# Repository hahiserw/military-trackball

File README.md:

# Military trackball

## Main document - main.pdf

## Youtube demo

## Gallery

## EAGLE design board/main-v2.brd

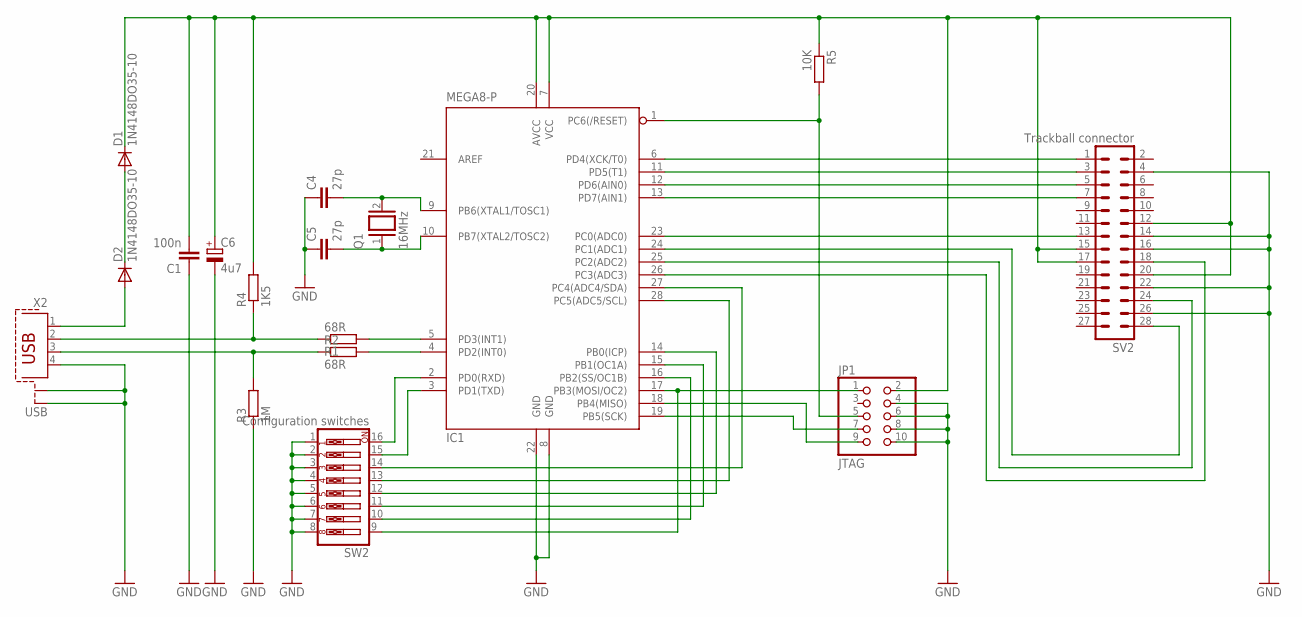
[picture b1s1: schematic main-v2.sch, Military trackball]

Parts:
C1: 100n; C025-025X050
C4, C5: 27p; C025-025X050
C6: 4u7; E2,5-5
D1, D2: 1N4148DO35-10; DO35-10
IC1: MEGA8-P; DIL28-3
JP1: JTAG; 2X05
Q1: 16MHz; QS
R1, R2: 68R; 0207/10
R3: 1M; 0207/10
R4: 1K5; 0207/10
R5: 10K; 0207/10
SV2: Trackball connector; MA14-2
SW2: Configuration switches; EDG-08
X2: USB; PN61729-S

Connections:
GND: C1.1, C4.1, C5.1, C6.-, IC1.8 (GND), IC1.22 (GND), JP1.4, JP1.6, JP1.8, JP1.10, R3.1, SV2.4, SV2.14, SV2.16, SV2.22, SV2.26, SW2.1, SW2.2, SW2.3, SW2.4, SW2.5, SW2.6, SW2.7, SW2.8, X2.4, X2.S1, X2.S2
unnamed: D1.A, D2.C
unnamed: IC1.5 (PD3(INT1)), R1.2
unnamed: IC1.4 (PD2(INT0)), R2.2
unnamed: R1.1, R4.1, X2.2
unnamed: R2.1, R3.2, X2.3
unnamed: IC1.12 (PD6(AIN0)), SV2.5
unnamed: C5.2, IC1.10 (PB7(XTAL2/TOSC2)), Q1.1
unnamed: C4.2, IC1.9 (PB6(XTAL1/TOSC1)), Q1.2
unnamed: IC1.11 (PD5(T1)), SV2.3
unnamed: IC1.6 (PD4(XCK/T0)), SV2.1
unnamed: IC1.23 (PC0(ADC0)), SV2.13
unnamed: IC1.13 (PD7(AIN1)), SV2.7
unnamed: IC1.25 (PC2(ADC2)), SV2.24
unnamed: IC1.26 (PC3(ADC3)), SV2.18
unnamed: IC1.1 (PC6(/RESET)), JP1.5, R5.2
unnamed: IC1.18 (PB4(MISO)), JP1.9
unnamed: IC1.19 (PB5(SCK)), JP1.7
unnamed: IC1.17 (PB3(MOSI/OC2)), JP1.1, SW2.9
unnamed: IC1.24 (PC1(ADC1)), SV2.28
unnamed: D2.A, X2.1
unnamed: IC1.16 (PB2(SS/OC1B)), SW2.10
unnamed: IC1.15 (PB1(OC1A)), SW2.11
unnamed: IC1.14 (PB0(ICP)), SW2.12
unnamed: IC1.2 (PD0(RXD)), SW2.16
unnamed: IC1.3 (PD1(TXD)), SW2.15
unnamed: IC1.27 (PC4(ADC4/SDA)), SW2.14
unnamed: IC1.28 (PC5(ADC5/SCL)), SW2.13
VCC: C1.2, C6.+, D1.C, IC1.7 (VCC), IC1.20 (AVCC), JP1.2, R4.2, R5.1, SV2.12, SV2.15, SV2.17, SV2.20

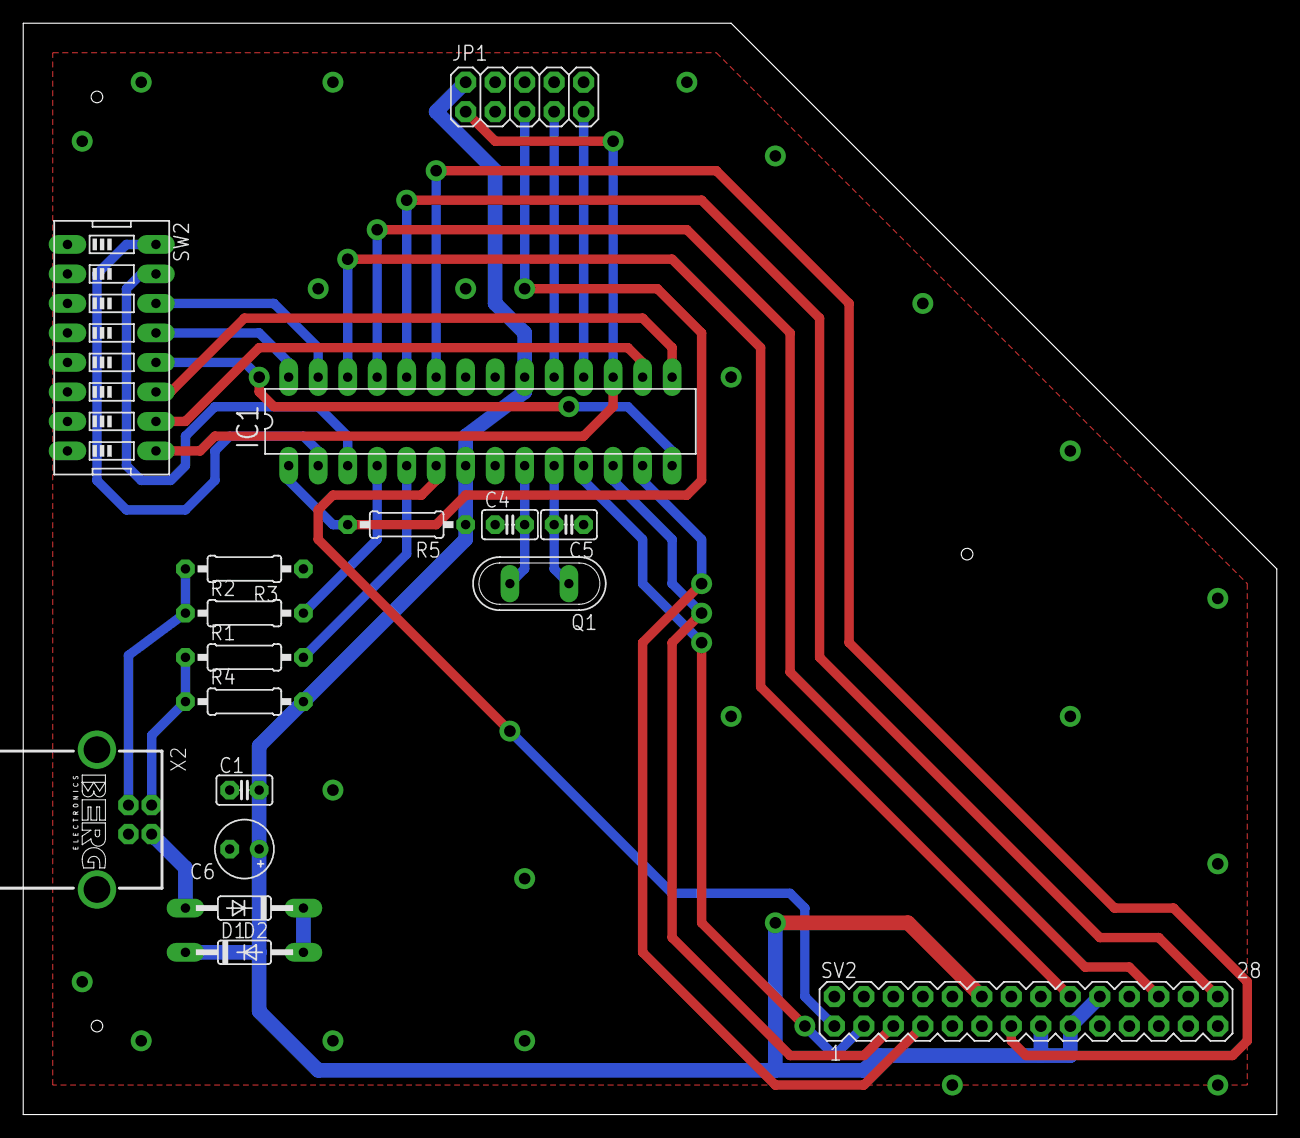
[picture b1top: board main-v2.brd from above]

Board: 2 copper layers, 108.0 x 94.0 mm, 17 parts (0 on the bottom side), 29 nets.

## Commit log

2019-10-25 add photos
2019-10-29 add main doc and another vid
2019-10-29 add board files
